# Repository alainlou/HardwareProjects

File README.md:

# Texas Instruments LM386 Amplifier Circuit

This project involved using a cheap solid-state audio amplifier chip to create an amplifier circuit intended to accompany my cheap electric guitar. The circuit contained resistors, capacitors (both non-polar and polar), a logarithmic potentiometer (for input volume control) and adaptors/plugs. A full spec sheet/schematic can be found here: http://www.ti.com/lit/ds/symlink/lm386.pdf. The circuit was based off of figures 12 and 14.

**I ended up overdriving the speaker and blowing it. In  it worked pretty well, but as you can see in  and , there is significant distortion after around 5 minutes of operation. Maybe when I build a high quality tube amp in the future I'll make sure not to mess things up lol.**

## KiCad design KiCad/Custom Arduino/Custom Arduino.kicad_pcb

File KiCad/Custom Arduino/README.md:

# Custom Arduino
<object data="https://github.com/alainlou/HardwareProjects/raw/master/KiCad/Custom%20Arduino/Custom%20Arduino.pdf" type="application/pdf" width="700px" height="700px">
    <embed src="https://github.com/alainlou/HardwareProjects/raw/master/KiCad/Custom%20Arduino/Custom%20Arduino.pdf">
        <p>This browser does not support PDFs. Please download the PDF to view it: <a href="https://github.com/alainlou/HardwareProjects/raw/master/KiCad/Custom%20Arduino/Custom%20Arduino.pdf">Download PDF</a>.</p>
    </embed>
</object>

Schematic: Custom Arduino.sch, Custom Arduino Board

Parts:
C1, C10: 100nF; C_0603_1608Metric
C2: 0.1 uF; C_0603_1608Metric
C3, C6, C8: 1uF; C_0603_1608Metric
C4, C5: 22pF; C_0603_1608Metric
C7: 47uF; CP_Elec_4x5.3
C9: 47uf; CP_Elec_4x5.3
D1, D2, D3: LED; LED_0603_1608Metric
D4: D1; D_0603_1608Metric
F1: Fuse; Fuse_1206_3216Metric
J1: UJ2-MBH-1-SMT-TR; USB_Mini_B_Female_UJ2-MBH-1-SMT-TR; MPN UJ2-MBH-1-SMT-TR; Digi-Key_PN 102-4003-1-ND
J2: Conn_02x02_Odd_Even; PinSocket_2x02_P2.54mm_Vertical
J3, J7: Conn_01x08; PinSocket_1x08_P2.54mm_Vertical
J4: Conn_01x06; PinSocket_1x06_P2.54mm_Vertical
J5: Conn_02x03_Odd_Even; PinSocket_2x03_P2.54mm_Vertical
J6: Conn_01x10; PinSocket_1x10_P2.54mm_Vertical
R1, R2, R3, R6, R7: 1k; R_0603_1608Metric
R4: 10k; R_0603_1608Metric
R5: 200; R_0603_1608Metric
SW1: SW_Push; SW_SPST_PTS645
U1: ATMEGA328P-PU; DIP-28_W7.62mm
U2: FT232RL-REEL; SSOP-28_W5.30mm; MPN FT232RL-REEL; Digi-Key_PN 768-1007-1-ND
U3: AZ1117EH-3.3TRG1; SOT-223
U4: MC33269DR2-5.0G; SOIC-8_W3.9mm
Y1: Crystal; Crystal_SMD_5032-2Pin_5.0x3.2mm

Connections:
3.3V: C8.1, J3.5, U3.1
5V: C9.1, C10.1, J2.3, U4.2, U4.3, U4.6, U4.7
5V_USB: F1.1, J2.1
A0: J4.6, U1.23 ((PCINT8/ADC0)PC0)
A1: J4.5, U1.24 ((PCINT9/ADC1)PC1)
A2: J4.4, U1.25 ((PCINT10/ADC2)PC2)
A3: J4.3, U1.26 ((PCINT11/ADC3)PC3)
A4: J4.2, J6.2, U1.27 ((PCINT12/SDA/ADC4)PC4)
A5: J4.1, J6.1, U1.28 ((PCINT13/SCL/ADC5)PC5)
D2: J7.6, U1.4 ((PCINT18/INT0)PD2)
D3: J7.5, U1.5 ((PCINT19/OC2B/INT1)PD3)
D4: J7.4, U1.6 ((PCINT20/XCK/T0)PD4)
D5: J7.3, U1.11 ((PCINT21/OC0B/T1)PD5)
D6: J7.2, U1.12 ((PCINT22/OC0A/AIN0)PD6)
D7: J7.1, U1.13 ((PCINT23/AIN1)PD7)
D8: J6.10, U1.14 ((PCINT0/CLKO/ICP1)PB0)
D9: J6.9, U1.15 ((PCINT1/OC1A)PB1)
D10: J6.8, U1.16 ((PCINT2/OC1B/~SS~)PB2)
D11: J5.4, J6.7, U1.17 ((PCINT3/OC2A/MOSI)PB3)
D12: J5.1, J6.6, U1.18 ((PCINT4/MISO)PB4)
D13: D3.2, J5.3, J6.5, U1.19 ((PCINT5/SCK)PB5)
DTR: C2.2, J3.6, J5.5, R7.1, U2.2
GND: C1.1, C3.1, C4.2, C5.2, C6.2, C7.2, C8.2, C9.2, C10.2, J1.5, J1.SH, J3.2, J3.3, J5.6, J6.4, R5.2, R7.2, SW1.2, U1.8 (GND), U1.22 (GND), U2.7, U2.18, U2.21, U2.25, U2.26, U3.2, U3.4, U4.1
unnamed: C2.1, R4.1, SW1.1, U1.1 ((PCINT14/~RESET~)PC6)
unnamed: C3.2, U2.17
unnamed: C4.1, U1.9 ((PCINT6/XTAL1/TOSC1)PB6), Y1.2
unnamed: C5.1, U1.10 ((PCINT7/XTAL2/TOSC2)PB7), Y1.1
unnamed: C7.1, D4.1, U4.4
unnamed: D1.1, U2.22
unnamed: D1.2, R1.1
unnamed: D2.1, U2.23
unnamed: D2.2, R2.1
unnamed: D3.1, R5.1
unnamed: F1.2, J1.1
unnamed: J1.2, U2.16
unnamed: J1.3, U2.15
unnamed: R3.2, U2.5
unnamed: R6.2, U2.1
RX: J7.8, R3.1, U1.2 ((PCINT16/RXD)PD0)
TX: J7.7, R6.1, U1.3 ((PCINT17/TXD)PD1)
VCC: C1.2, J2.2, J2.4, J3.4, J3.7, J5.2, J6.3, R1.2, R2.2, R4.2, U1.7 (VCC), U1.20 (AVCC), U1.21 (AREF), U2.4, U2.19, U2.20
Vin: C6.1, D4.2, J3.1, U3.3

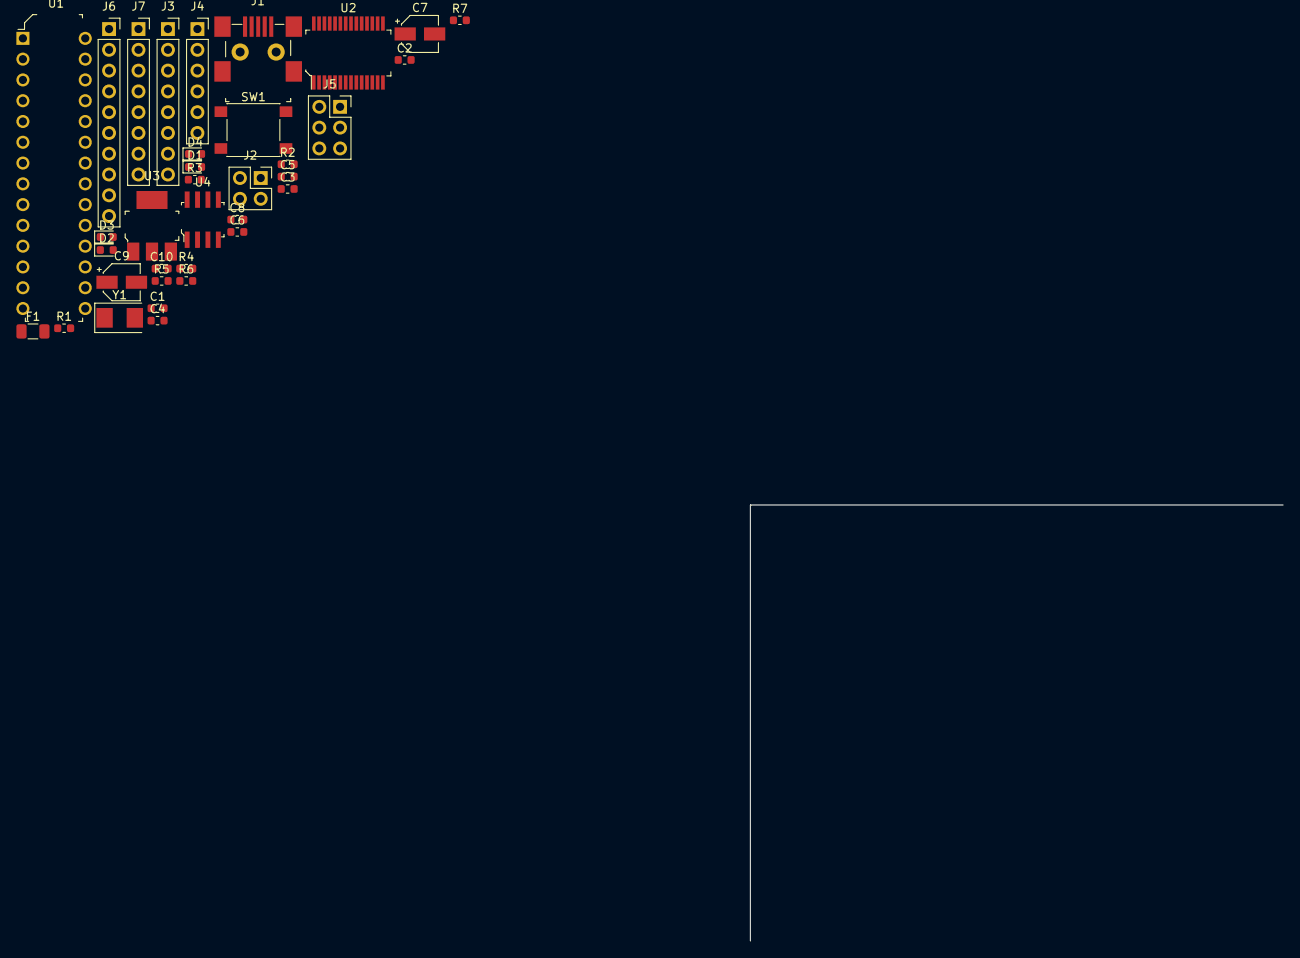
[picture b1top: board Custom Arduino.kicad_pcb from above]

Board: 2 copper layers, 35 parts (0 on the bottom side), 42 nets, no tracks yet.

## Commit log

2018-09-18 rEaDmE
2018-09-18 README and filename changes
2018-09-18 pictures!
2018-09-18 it'd be nice if i formatted it correctly the first time
2018-09-18 it'd be nice if i formatted it correctly the second time
2018-09-18 it'd be nice if i formatted it correctly the third time
2018-09-18 spelling and grammar!
2018-09-19 links on the LM386 project
2018-09-19 links to raw files themselves
2018-10-01 CAD stuff
2018-10-01 added readme to CAD stuff
2018-10-03 reorganized custom arduino stuff
2018-10-03 cut out the bs and add embedded pdf
2018-10-04 raw not blob
2018-10-04 removed temp files
2018-10-04 removed temp files actually
2018-10-25 get rid of the giant photo
2018-10-25 I still need a README
2019-01-02 changed README
2019-05-14 seperate project
2019-05-14 Update README.md
    new url
